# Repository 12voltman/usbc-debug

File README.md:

# usbc-debug
USB-C dongle that breaks out 9 extra pins, allowing for easy debugging/programming of devices using one connector.  Also includes eagle part for DUT-side connectors.

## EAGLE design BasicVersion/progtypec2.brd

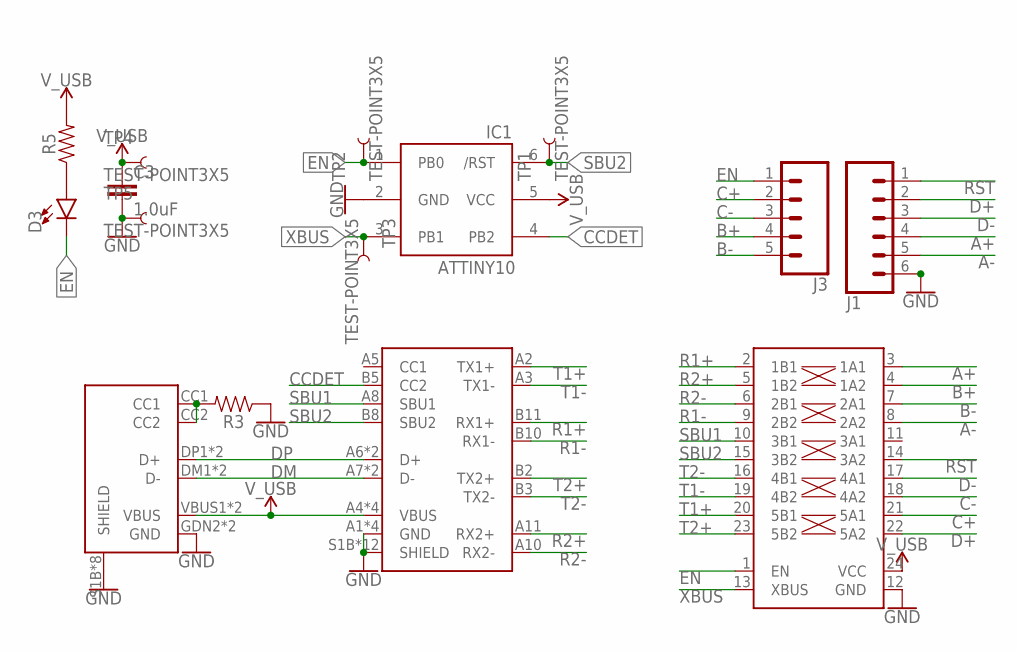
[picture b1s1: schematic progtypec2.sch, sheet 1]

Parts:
C3: 1.0uF; 0603
D3: LED0603; LED-0603
IC1: ATTINY10; SOT23-6
J1: CONN_06NO_SILK_FEMALE_PTH; 1X06_NO_SILK
J3: CONN_05NO_SILK; 1X05_NO_SILK
R3, R5: 0603
TP1, TP2, TP3, TP4, TP5: TEST-POINT3X5; PAD.03X.05
U$1: USB-C-HORZ-F; USB-C_24PIN_HORZ-F-UNTESTED
U$2: USB-C_USB2ONLY-HORZ-F_12P; USB-C_12PIN_HORZ-F
U$3: SN74CBT3383C; TSSOP24

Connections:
A+: J1.4, U$3.3 (1A1)
A-: J1.5, U$3.8 (2A2)
B+: J3.4, U$3.4 (1A2)
B-: J3.5, U$3.7 (2A1)
C+: J3.2, U$3.21 (5A1)
C-: J3.3, U$3.18 (4A2)
CCDET: IC1.4 (PB2), U$1.B5 (CC2)
CCUP: R3.2, U$2.CC1, U$2.CC2
D+: J1.2, U$3.22 (5A2)
D-: J1.3, U$3.17 (4A1)
DM: U$1.A7 (D-), U$1.B7 (D-), U$2.DM1 (D-), U$2.DM2 (D-)
DP: U$1.A6 (D+), U$1.B6 (D+), U$2.DP1 (D+), U$2.DP2 (D+)
EN: D3.C, IC1.1 (PB0), J3.1, TP2.P$1, U$3.1 (EN)
GND: C3.2, IC1.2 (GND), J1.6, R3.1, TP5.P$1, U$1.A1 (GND), U$1.A12 (GND), U$1.B1 (GND), U$1.B12 (GND), U$1.S1B (SHIELD), U$1.S1T (SHIELD), U$1.S2B (SHIELD), U$1.S2T (SHIELD), U$1.S3B (SHIELD), U$1.S3T (SHIELD), U$1.S4B (SHIELD), U$1.S4T (SHIELD), U$1.S5B (SHIELD), U$1.S5T (SHIELD), U$1.S6B (SHIELD), U$1.S6T (SHIELD), U$2.GDN2 (GND), U$2.GND1 (GND), U$2.S1B (SHIELD), U$2.S1T (SHIELD), U$2.S2B (SHIELD), U$2.S2T (SHIELD), U$2.S3B (SHIELD), U$2.S3T (SHIELD), U$2.S4B (SHIELD), U$2.S4T (SHIELD), U$3.12 (GND)
unnamed: D3.A, R5.1
R1+: U$1.B11 (RX1+), U$3.2 (1B1)
R1-: U$1.B10 (RX1-), U$3.9 (2B2)
R2+: U$1.A11 (RX2+), U$3.5 (1B2)
R2-: U$1.A10 (RX2-), U$3.6 (2B1)
RST: J1.1, U$3.14 (3A2)
SBU1: U$1.A8 (SBU1), U$3.10 (3B1)
SBU2: IC1.6 (/RST), TP1.P$1, U$1.B8 (SBU2), U$3.15 (3B2)
T1+: U$1.A2 (TX1+), U$3.20 (5B1)
T1-: U$1.A3 (TX1-), U$3.19 (4B2)
T2+: U$1.B2 (TX2+), U$3.23 (5B2)
T2-: U$1.B3 (TX2-), U$3.16 (4B1)
V_USB: C3.1, IC1.5 (VCC), R5.2, TP4.P$1, U$1.A4 (VBUS), U$1.A9 (VBUS), U$1.B4 (VBUS), U$1.B9 (VBUS), U$2.VBUS1 (VBUS), U$2.VBUS2 (VBUS), U$3.24 (VCC)
XBUS: IC1.3 (PB1), TP3.P$1, U$3.13 (XBUS)

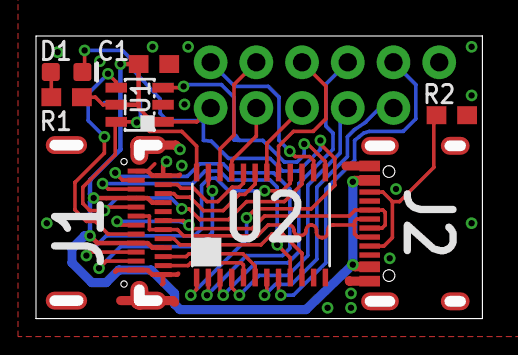
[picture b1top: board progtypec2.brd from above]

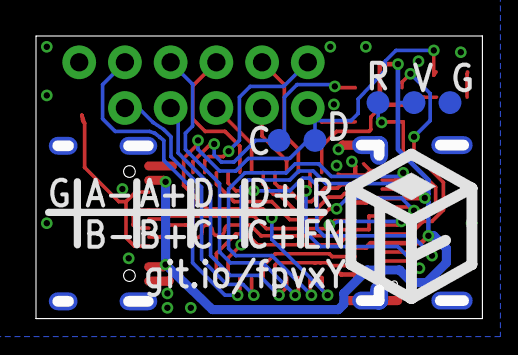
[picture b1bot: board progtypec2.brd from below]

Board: 2 copper layers, 24.8 x 15.7 mm, 15 parts (5 on the bottom side), 28 nets.

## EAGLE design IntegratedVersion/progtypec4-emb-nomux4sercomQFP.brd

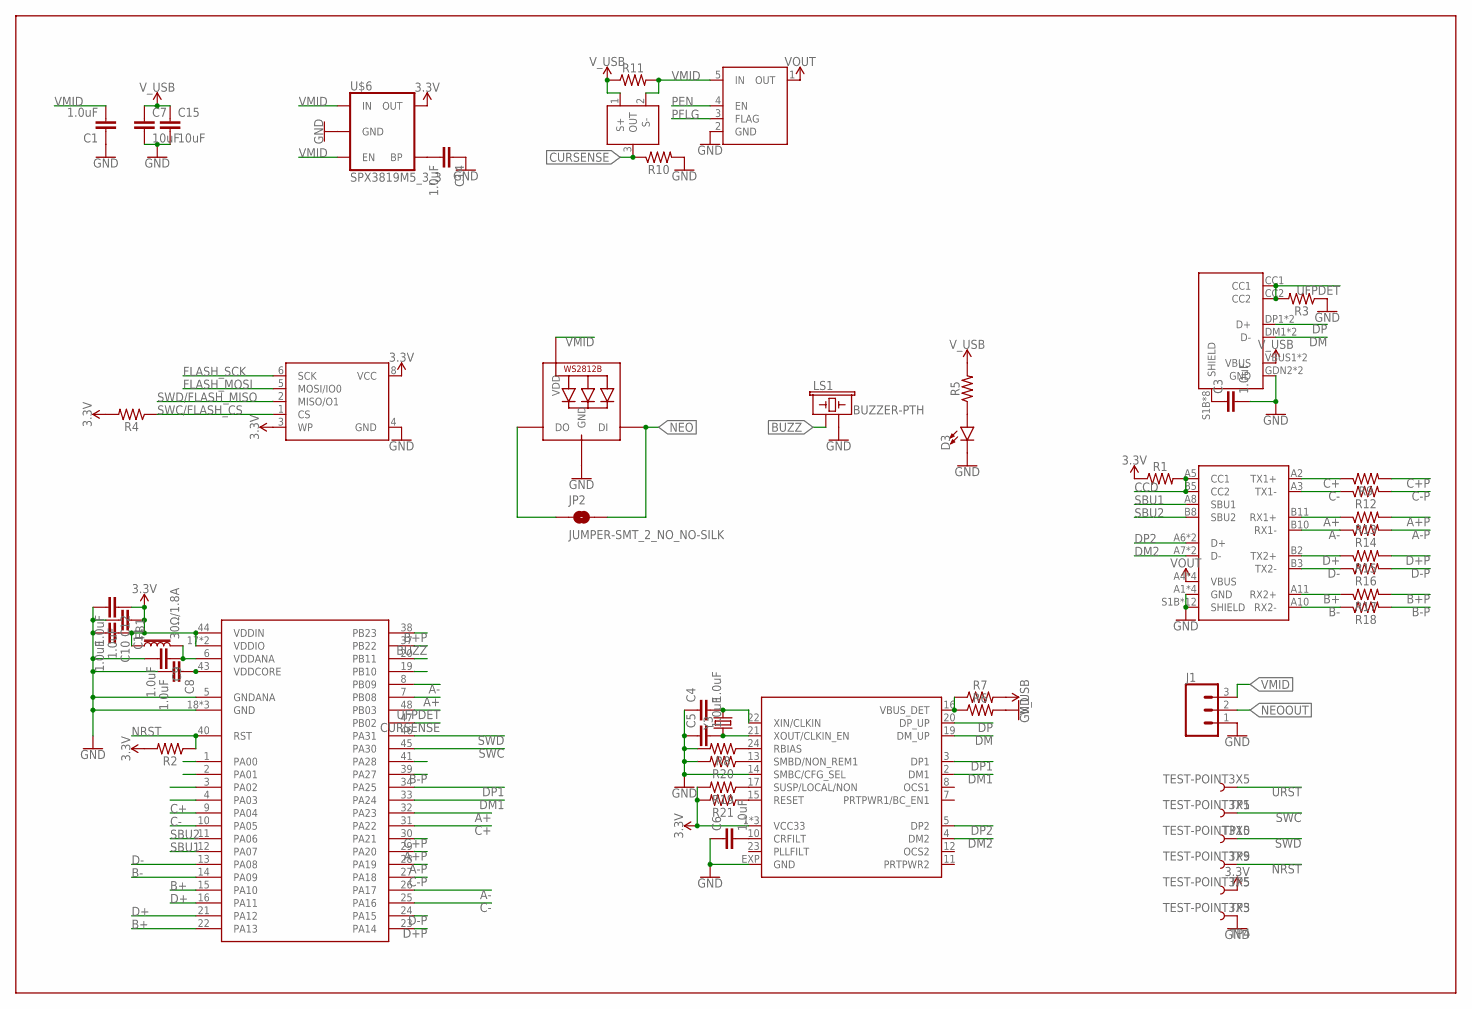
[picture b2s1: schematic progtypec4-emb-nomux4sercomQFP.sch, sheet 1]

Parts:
C1, C3, C4, C5, C6, C8, C9, C10, C11, C12, C14: 1.0uF; 0603
C7, C15: 10uF; 0805
D3: LED0603; LED-0603
FB1: 30Ω/1.8A; 0603
J1: CONN_03SMD_RA_MALE; 1X03_SMD_RA_MALE
JP2: JUMPER-SMT_2_NO_NO-SILK; SMT-JUMPER_2_NO_NO-SILK
LED1: WS2812B3535; LED3535
LS1: BUZZER-PTH; BUZZER-12MM
R1, R2, R3, R4, R5, R6, R7, R8, R9, R10, R12, R13, R14, R15, R16, R17, R18, R19, R20, R21: 0603
R11: 1206
TP1, TP3, TP4, TP5, TP9, TP10: TEST-POINT3X5; PAD.03X.05
U$1: USB-C-HORZ-F; USB-C_24PIN_HORZ-F-UNTESTED
U$2: USB-C_USB2ONLY-HORZ-F_12P; USB-C_12PIN_HORZ-F
U$3: ZXCT1107; SOT23-3
U$4: AP22804/14*W5; SOT23-5
U$5: USB2422; QFN24_4X4_MOREPAD
U$6: SPX3819M5_3_3; SOT23-5
U$7: GD25D10C/05CE; UDFN8
U$9: ATSAMD2G1A-A; TQFP48_7X7
Y3: CRYSTALSMD-3.2X2.5; CRYSTAL-SMD-3.2X2.5MM

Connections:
3.3V: C10.1, C11.1, C12.1, FB1.1, R1.1, R2.2, R4.2, R19.2, R21.2, TP3.P$1, U$5.1 (VCC33), U$5.9 (VCC33), U$5.18 (VCC33), U$6.5 (OUT), U$7.3 (WP), U$7.8 (VCC), U$9.17 (VDDIO), U$9.36 (VDDIO), U$9.44 (VDDIN)
A+: R13.1, U$1.B11 (RX1+), U$9.7 (PB08), U$9.32 (PA23)
A+P: R13.2, U$9.29 (PA20)
A-: R14.1, U$1.B10 (RX1-), U$9.8 (PB09), U$9.26 (PA17)
A-P: R14.2, U$9.28 (PA19)
B+: R17.1, U$1.A11 (RX2+), U$9.15 (PA10), U$9.22 (PA13)
B+P: R17.2, U$9.38 (PB23)
B-: R18.1, U$1.A10 (RX2-), U$9.14 (PA09)
B-P: R18.2, U$9.39 (PA27)
BUZZ: LS1.+ (1), U$9.37 (PB22)
C+: R9.1, U$1.A2 (TX1+), U$9.9 (PA04), U$9.31 (PA22)
C+P: R9.2, U$9.30 (PA21)
C-: R12.1, U$1.A3 (TX1-), U$9.10 (PA05), U$9.25 (PA16)
C-P: R12.2, U$9.27 (PA18)
CCD: R1.2, U$1.A5 (CC1), U$1.B5 (CC2)
CURSENSE: R10.1, U$3.3 (OUT), U$9.47 (PB02)
D+: R15.1, U$1.B2 (TX2+), U$9.16 (PA11), U$9.21 (PA12)
D+P: R15.2, U$9.23 (PA14)
D-: R16.1, U$1.B3 (TX2-), U$9.13 (PA08)
D-P: R16.2, U$9.24 (PA15)
DM: U$2.DM1 (D-), U$2.DM2 (D-), U$5.19 (DM_UP)
DM1: U$5.2 (DM1), U$9.33 (PA24)
DM2: U$1.A7 (D-), U$1.B7 (D-), U$5.4 (DM2)
DP: U$2.DP1 (D+), U$2.DP2 (D+), U$5.20 (DP_UP)
DP1: U$5.3 (DP1), U$9.34 (PA25)
DP2: U$1.A6 (D+), U$1.B6 (D+), U$5.5 (DP2)
FLASH_MOSI: U$7.5 (MOSI/IO0)
FLASH_SCK: U$7.6 (SCK)
GND: C1.1, C3.2, C4.1, C5.1, C6.1, C7.2, C8.2, C9.2, C10.2, C11.2, C12.2, C14.1, C15.2, D3.C, J1.1, LED1.4 (GND), LS1.- (2), R3.1, R6.2, R8.2, R10.2, R20.2, TP4.P$1, U$1.A1 (GND), U$1.A12 (GND), U$1.B1 (GND), U$1.B12 (GND), U$1.S1B (SHIELD), U$1.S1T (SHIELD), U$1.S2B (SHIELD), U$1.S2T (SHIELD), U$1.S3B (SHIELD), U$1.S3T (SHIELD), U$1.S4B (SHIELD), U$1.S4T (SHIELD), U$1.S5B (SHIELD), U$1.S5T (SHIELD), U$1.S6B (SHIELD), U$1.S6T (SHIELD), U$2.GDN2 (GND), U$2.GND1 (GND), U$4.2 (GND), U$5.14 (SMBC/CFG_SEL), U$5.EXP (GND), U$6.2 (GND), U$7.4 (GND), U$9.5 (GNDANA), U$9.18 (GND), U$9.35 (GND), U$9.42 (GND)
unnamed: D3.A, R5.1
unnamed: R6.1, R7.1, U$5.16 (VBUS_DET)
unnamed: R8.1, U$5.24 (RBIAS)
unnamed: C4.2, U$5.22 (XIN/CLKIN), Y3.3 (2)
unnamed: C5.2, U$5.21 (XOUT/CLKIN_EN), Y3.1
unnamed: R19.1, U$5.17 (SUSP/LOCAL/NON)
unnamed: C6.2, U$5.10 (CRFILT)
unnamed: R20.1, U$5.13 (SMBD/NON_REM1)
unnamed: C3.1, U$2.S1B (SHIELD), U$2.S1T (SHIELD), U$2.S2B (SHIELD), U$2.S2T (SHIELD), U$2.S3B (SHIELD), U$2.S3T (SHIELD), U$2.S4B (SHIELD), U$2.S4T (SHIELD)
unnamed: C14.2, U$6.4 (BP)
NEO: JP2.2, LED1.1 (DI)
NEOOUT: J1.2, JP2.1, LED1.3 (DO)
NRST: R2.1, TP5.P$1, U$9.40 (RST)
PEN: U$4.4 (EN)
PFLG: U$4.3 (FLAG)
SBU1: U$1.A8 (SBU1), U$9.12 (PA07)
SBU2: U$1.B8 (SBU2), U$9.11 (PA06)
SWC: TP10.P$1, U$9.45 (PA30)
SWC/FLASH_CS: R4.1, U$7.1 (CS)
SWD: TP9.P$1, U$9.46 (PA31)
SWD/FLASH_MISO: U$7.2 (MISO/O1)
UFPDET: R3.2, U$2.CC1, U$2.CC2, U$9.48 (PB03)
URST: R21.1, TP1.P$1, U$5.15 (RESET)
VCCA: C9.1, FB1.2, U$9.6 (VDDANA)
VCORE: C8.1, U$9.43 (VDDCORE)
VMID: C1.2, J1.3, LED1.2 (VDD), R11.2, U$3.2 (S-), U$4.5 (IN), U$6.1 (IN), U$6.3 (EN)
VOUT: U$1.A4 (VBUS), U$1.A9 (VBUS), U$1.B4 (VBUS), U$1.B9 (VBUS), U$4.1 (OUT)
V_USB: C7.1, C15.1, R5.2, R7.2, R11.1, U$2.VBUS1 (VBUS), U$2.VBUS2 (VBUS), U$3.1 (S+)

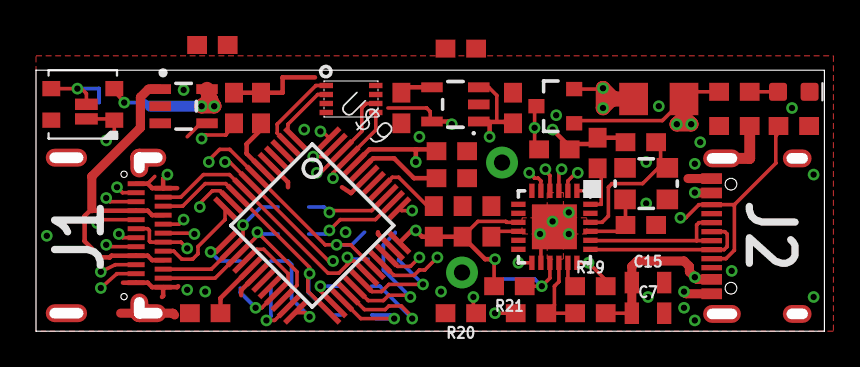
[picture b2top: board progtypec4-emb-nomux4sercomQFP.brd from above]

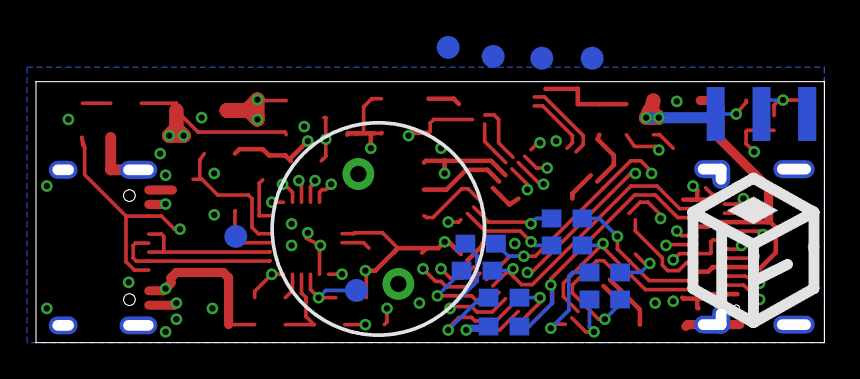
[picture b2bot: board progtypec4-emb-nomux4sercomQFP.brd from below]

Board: 4 copper layers, 43.8 x 14.5 mm, 55 parts (16 on the bottom side), 52 nets.

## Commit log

2019-07-16 Oops, actually commited the project files this time

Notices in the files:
parts and their libraries:
SparkFun-Capacitors: Licensing: Creative Commons ShareAlike 4.0 International - https://creativecommons.org/licenses/by-sa/4.0
